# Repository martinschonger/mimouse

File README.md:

# Micromouse

In this student project at the Technical University of Munich we engineered a mobile robot from scratch. The final report is available at [report.pdf](report.pdf).

This repository currently contains the Schematic and PCB design files ([eagle/](eagle/)), PDFs thereof ([schematic_pcb_pdfs/](schematic_pcb_pdfs/)), and some MATLAB scripts concerning trajectory generation ([matlab/](matlab/)).

TODO: Add (additional) C, CAD, MATLAB/Simulink, and potentially some PCB library files.

<br/>

Copyright © 2020 Theo Goldfuss, Ran Gu, Niels Schlegel, Martin Schonger  
This work is licensed under the GPLv3.

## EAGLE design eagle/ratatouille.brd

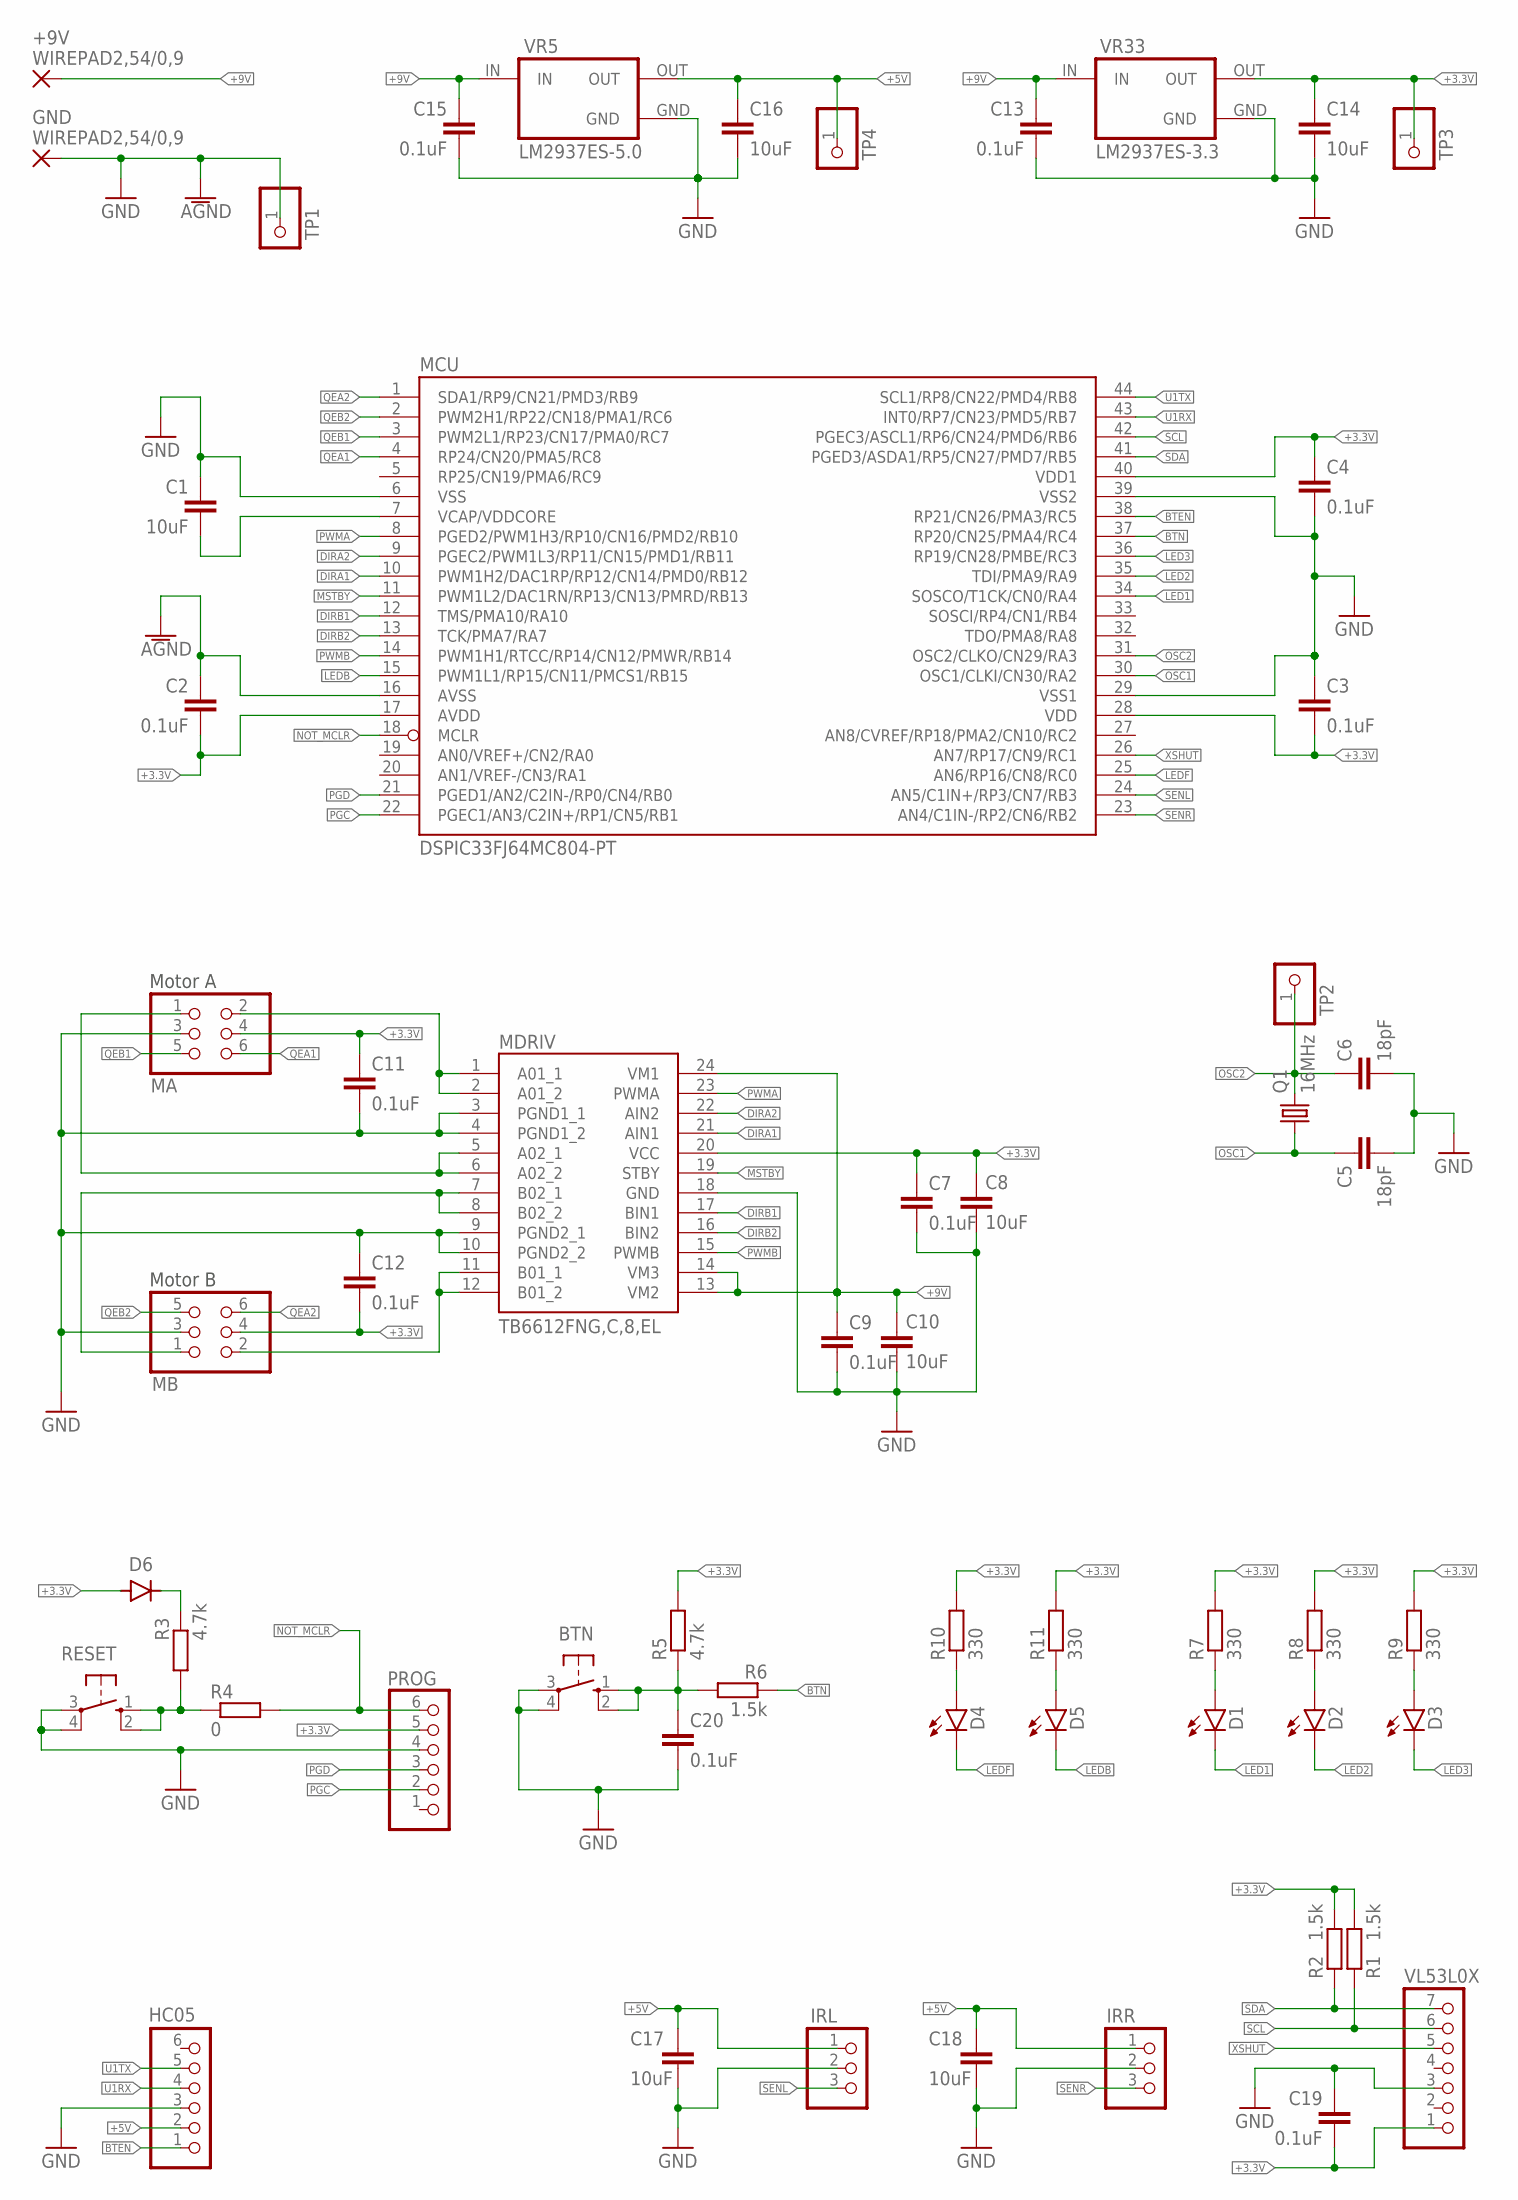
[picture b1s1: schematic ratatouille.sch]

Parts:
+9V: WIREPAD2,54/0,9; 2,54/0,9
BTN: 10-XX; B3F-10XX
C1, C8, C10, C14, C16: 10uF; C3216
C2, C3, C4, C7, C9, C11, C12, C13, C15, C19, C20: 0.1uF; C0805
C5, C6: 18pF; C0805
C17, C18: 10uF; C0805
D1, D2, D3: LEDCHIP-LED0805; CHIP-LED0805
D4, D5: LED3MM
D6: DIODE-SOD123; SOD123
GND: WIREPAD2,54/0,9; 2,54/0,9
HC05: PINHD-1X6; 1X06
IRL: PINHD-1X3; 1X03
IRR: PINHD-1X3; 1X03
MA: PINHD-2X3; 2X03
MB: PINHD-2X3; 2X03
MCU: DSPIC33FJ64MC804-PT; TQFP44
MDRIV: TB6612FNG,C,8,EL; SOP65P760X160-24N
PROG: PINHD-1X6/90; 1X06/90
Q1: 16MHz; HC49U-V
R1, R2, R6: 1.5k; R0805
R3, R5: 4.7k; R0805
R4: 0; R0805
R7, R8, R9, R10, R11: 330; R0805
RESET: 10-XX; B3F-10XX
TP1, TP2, TP3, TP4: PINHD-1X1; 1X01
VL53L0X: PINHD-1X7; 1X07
VR5: LM2937ES-5.0; TO263
VR33: LM2937ES-3.3; TO263

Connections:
+3.3V: C2.1, C3.1, C4.1, C7.1, C8.1, C11.2, C12.2, C14.1, C19.1, D6.A, MA.4, MB.4, MCU.17 (AVDD), MCU.28 (VDD), MCU.40 (VDD1), MDRIV.20 (VCC), PROG.5, R1.2, R2.2, R5.2, R7.2, R8.2, R9.2, R10.2, R11.2, TP3.1, VL53L0X.1, VR33.OUT
+5V: C16.1, C17.1, C18.1, HC05.2, IRL.1, IRR.1, TP4.1, VR5.OUT
+9V: +9V.1, C9.1, C10.1, C13.1, C15.1, MDRIV.13 (VM2), MDRIV.14 (VM3), MDRIV.24 (VM1), VR5.IN, VR33.IN
BTEN: HC05.1, MCU.38 (RP21/CN26/PMA3/RC5)
BTN: MCU.37 (RP20/CN25/PMA4/RC4), R6.1
DIRA1: MCU.10 (PWM1H2/DAC1RP/RP12/CN14/PMD0/RB12), MDRIV.21 (AIN1)
DIRA2: MCU.9 (PGEC2/PWM1L3/RP11/CN15/PMD1/RB11), MDRIV.22 (AIN2)
DIRB1: MCU.12 (TMS/PMA10/RA10), MDRIV.17 (BIN1)
DIRB2: MCU.13 (TCK/PMA7/RA7), MDRIV.16 (BIN2)
GND: BTN.3, BTN.4 (P1), C1.2, C2.2, C3.2, C4.2, C5.1, C6.1, C7.2, C8.2, C9.2, C10.2, C11.1, C12.1, C13.2, C14.2, C15.2, C16.2, C17.2, C18.2, C19.2, C20.2, GND.1, HC05.3, IRL.2, IRR.2, MA.3, MB.3, MCU.6 (VSS), MCU.16 (AVSS), MCU.29 (VSS1), MCU.39 (VSS2), MDRIV.3 (PGND1_1), MDRIV.4 (PGND1_2), MDRIV.9 (PGND2_1), MDRIV.10 (PGND2_2), MDRIV.18 (GND), PROG.4, RESET.3, RESET.4 (P1), TP1.1, VL53L0X.3, VR5.GND, VR5.GND@ (GND), VR33.GND, VR33.GND@ (GND)
LED1: D1.C, MCU.34 (SOSCO/T1CK/CN0/RA4)
LED2: D2.C, MCU.35 (TDI/PMA9/RA9)
LED3: D3.C, MCU.36 (RP19/CN28/PMBE/RC3)
LEDB: D5.K (C), MCU.15 (PWM1L1/RP15/CN11/PMCS1/RB15)
LEDF: D4.K (C), MCU.25 (AN6/RP16/CN8/RC0)
MSTBY: MCU.11 (PWM1L2/DAC1RN/RP13/CN13/PMRD/RB13), MDRIV.19 (STBY)
unnamed: BTN.1 (S), BTN.2 (S1), C20.1, R5.1, R6.2
unnamed: R3.1, R4.1, RESET.1 (S), RESET.2 (S1)
unnamed: D2.A, R8.1
unnamed: MA.2, MDRIV.1 (A01_1), MDRIV.2 (A01_2)
unnamed: D1.A, R7.1
unnamed: MA.1, MDRIV.5 (A02_1), MDRIV.6 (A02_2)
unnamed: D3.A, R9.1
unnamed: D6.C, R3.2
unnamed: MB.2, MDRIV.11 (B01_1), MDRIV.12 (B01_2)
unnamed: MB.1, MDRIV.7 (B02_1), MDRIV.8 (B02_2)
unnamed: D4.A, R10.1
unnamed: D5.A, R11.1
NOT_MCLR: MCU.18 (MCLR), PROG.6, R4.2
OSC1: C5.2, MCU.30 (OSC1/CLKI/CN30/RA2), Q1.1
OSC2: C6.2, MCU.31 (OSC2/CLKO/CN29/RA3), Q1.2, TP2.1
PGC: MCU.22 (PGEC1/AN3/C2IN+/RP1/CN5/RB1), PROG.2
PGD: MCU.21 (PGED1/AN2/C2IN-/RP0/CN4/RB0), PROG.3
PWMA: MCU.8 (PGED2/PWM1H3/RP10/CN16/PMD2/RB10), MDRIV.23 (PWMA)
PWMB: MCU.14 (PWM1H1/RTCC/RP14/CN12/PMWR/RB14), MDRIV.15 (PWMB)
QEA1: MA.6, MCU.4 (RP24/CN20/PMA5/RC8)
QEA2: MB.6, MCU.1 (SDA1/RP9/CN21/PMD3/RB9)
QEB1: MA.5, MCU.3 (PWM2L1/RP23/CN17/PMA0/RC7)
QEB2: MB.5, MCU.2 (PWM2H1/RP22/CN18/PMA1/RC6)
SCL: MCU.42 (PGEC3/ASCL1/RP6/CN24/PMD6/RB6), R1.1, VL53L0X.6
SDA: MCU.41 (PGED3/ASDA1/RP5/CN27/PMD7/RB5), R2.1, VL53L0X.7
SENL: IRL.3, MCU.24 (AN5/C1IN+/RP3/CN7/RB3)
SENR: IRR.3, MCU.23 (AN4/C1IN-/RP2/CN6/RB2)
U1RX: HC05.4, MCU.43 (INT0/RP7/CN23/PMD5/RB7)
U1TX: HC05.5, MCU.44 (SCL1/RP8/CN22/PMD4/RB8)
VCAP/VDDCORE: C1.1, MCU.7 (VCAP/VDDCORE)
XSHUT: MCU.26 (AN7/RP17/CN9/RC1), VL53L0X.5

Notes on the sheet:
Motor A
Motor B

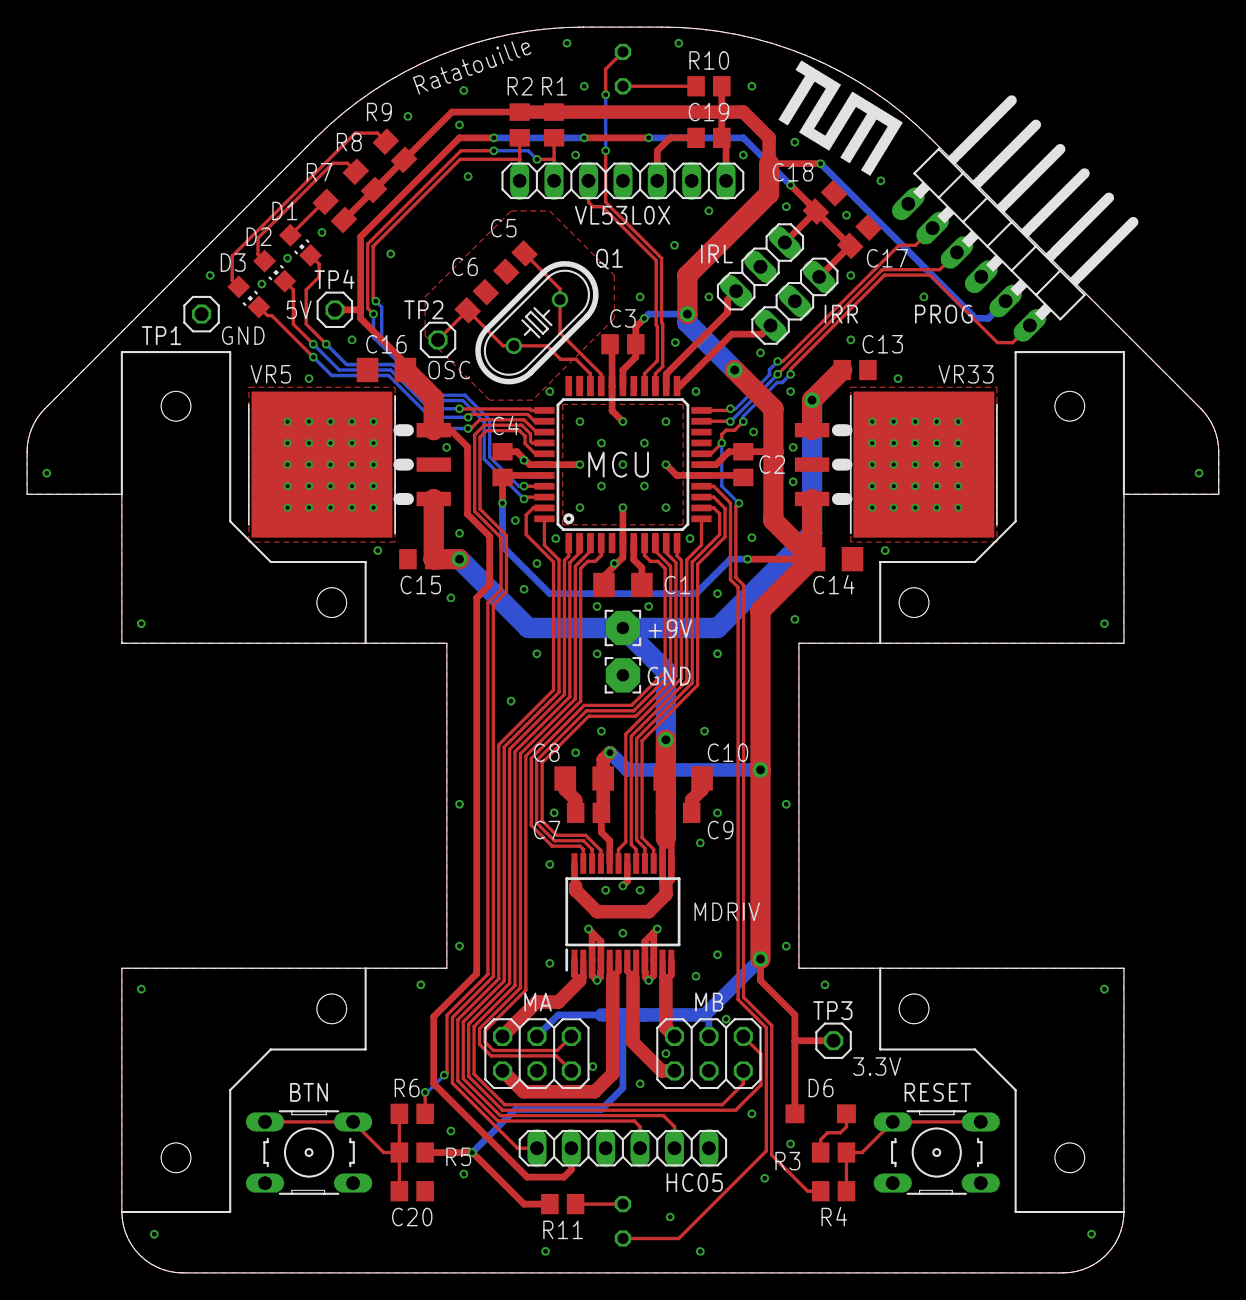
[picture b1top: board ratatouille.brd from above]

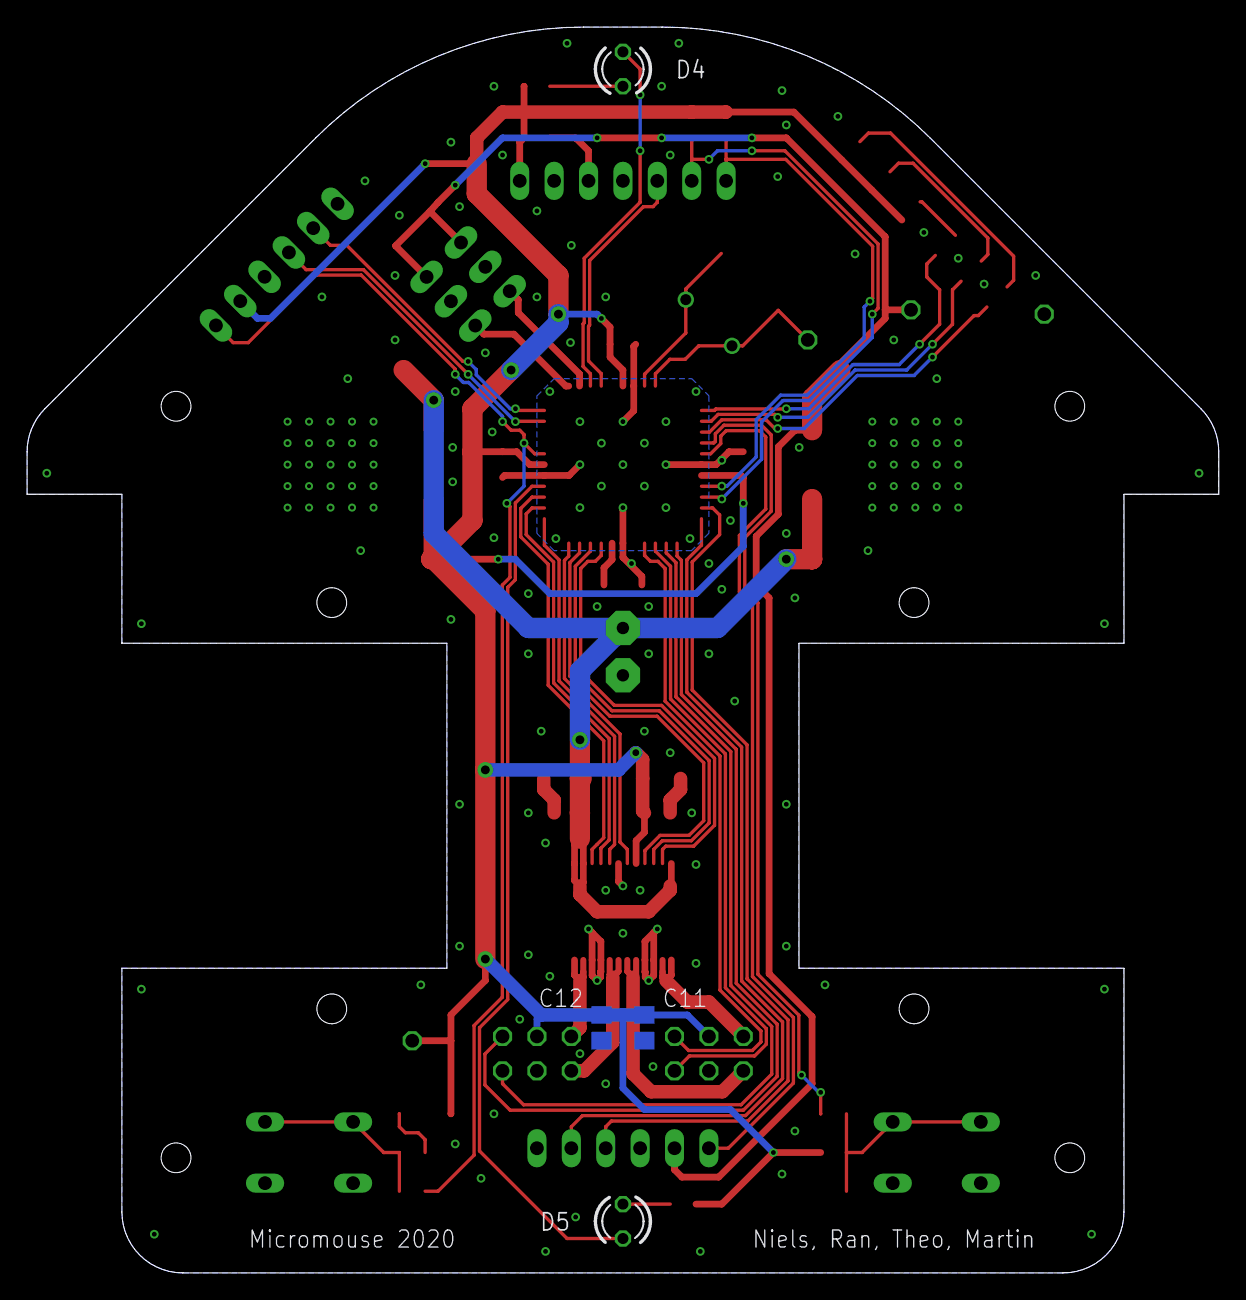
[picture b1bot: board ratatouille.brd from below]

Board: 2 copper layers, 88.0 x 92.0 mm, 57 parts (4 on the bottom side), 47 nets.

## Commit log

2023-04-18 Add copyright notice to README.md.
2023-04-19 Add .gitignore
2023-04-19 Add final report PDF. Add schematic, PCB, and some MATLAB files. Update README.
